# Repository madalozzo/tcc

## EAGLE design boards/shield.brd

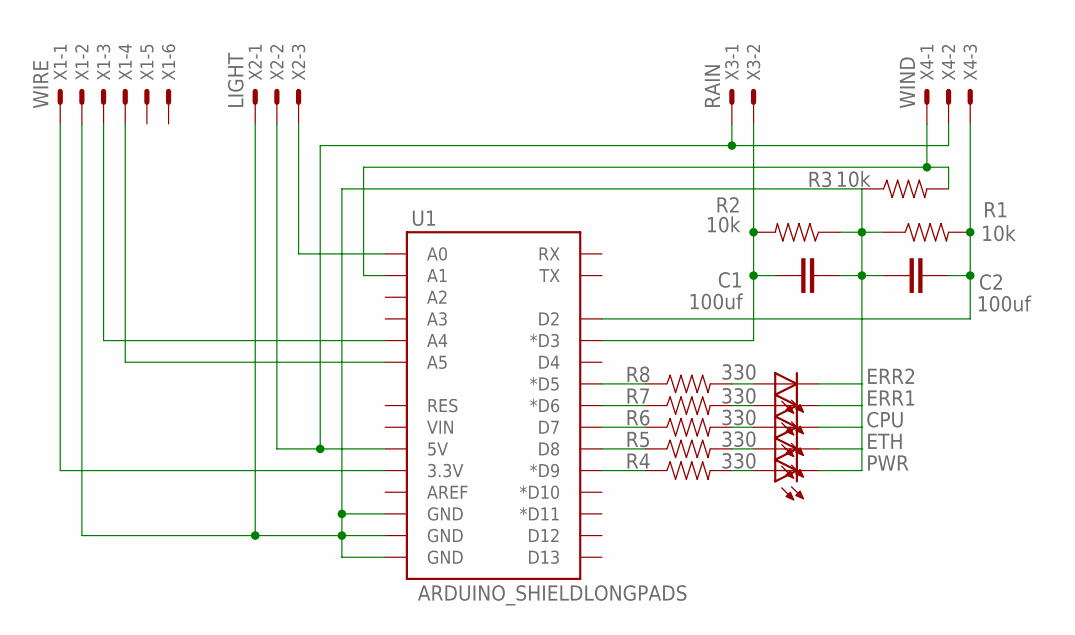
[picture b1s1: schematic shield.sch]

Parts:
C1, C2: 100uf; CAP-PTH-SMALL-KIT
CPU: LED3MM
ERR1, ERR2: LED3MM
ETH: LED3MM
PWR: LED3MM
R1, R2, R3: 10k; AXIAL-0.3-KIT
R4, R5, R6, R7, R8: 330; AXIAL-0.3-KIT
U1: ARDUINO_SHIELDLONGPADS; DUEMILANOVE_SHIELD_LONGPADS
X1: WIRE; 22-23-2061
X2: LIGHT; 22-23-2031
X3: RAIN; 22-23-2021
X4: WIND; 22-23-2031

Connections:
GND: C1.2, C2.1, CPU.K (C), ERR1.K (C), ERR2.K (C), ETH.K (C), PWR.K (C), R1.P$1 (1), R2.P$1 (1), R3.P$1 (1), U1.GND@0 (GND), U1.GND@1 (GND), U1.GND@2 (GND), X1.2, X2.1
INT0: C2.2, R1.P$2 (2), U1.D2, X4.3
INT1: C1.1, R2.P$2 (2), U1.D3 (*D3), X3.2
unnamed: U1.3.3V, X1.1
unnamed: R8.P$1 (1), U1.D5 (*D5)
unnamed: U1.5V, X2.2, X3.1, X4.2
unnamed: U1.A0, X2.3
unnamed: R3.P$2 (2), U1.A1, X4.1
unnamed: R7.P$1 (1), U1.D6 (*D6)
unnamed: R6.P$1 (1), U1.D7
unnamed: ERR2.A, R8.P$2 (2)
unnamed: R5.P$1 (1), U1.D8
unnamed: ERR1.A, R7.P$2 (2)
unnamed: CPU.A, R6.P$2 (2)
unnamed: ETH.A, R5.P$2 (2)
unnamed: PWR.A, R4.P$2 (2)
unnamed: R4.P$1 (1), U1.D9 (*D9)
SCL: U1.A5, X1.4
SDA: U1.A4, X1.3

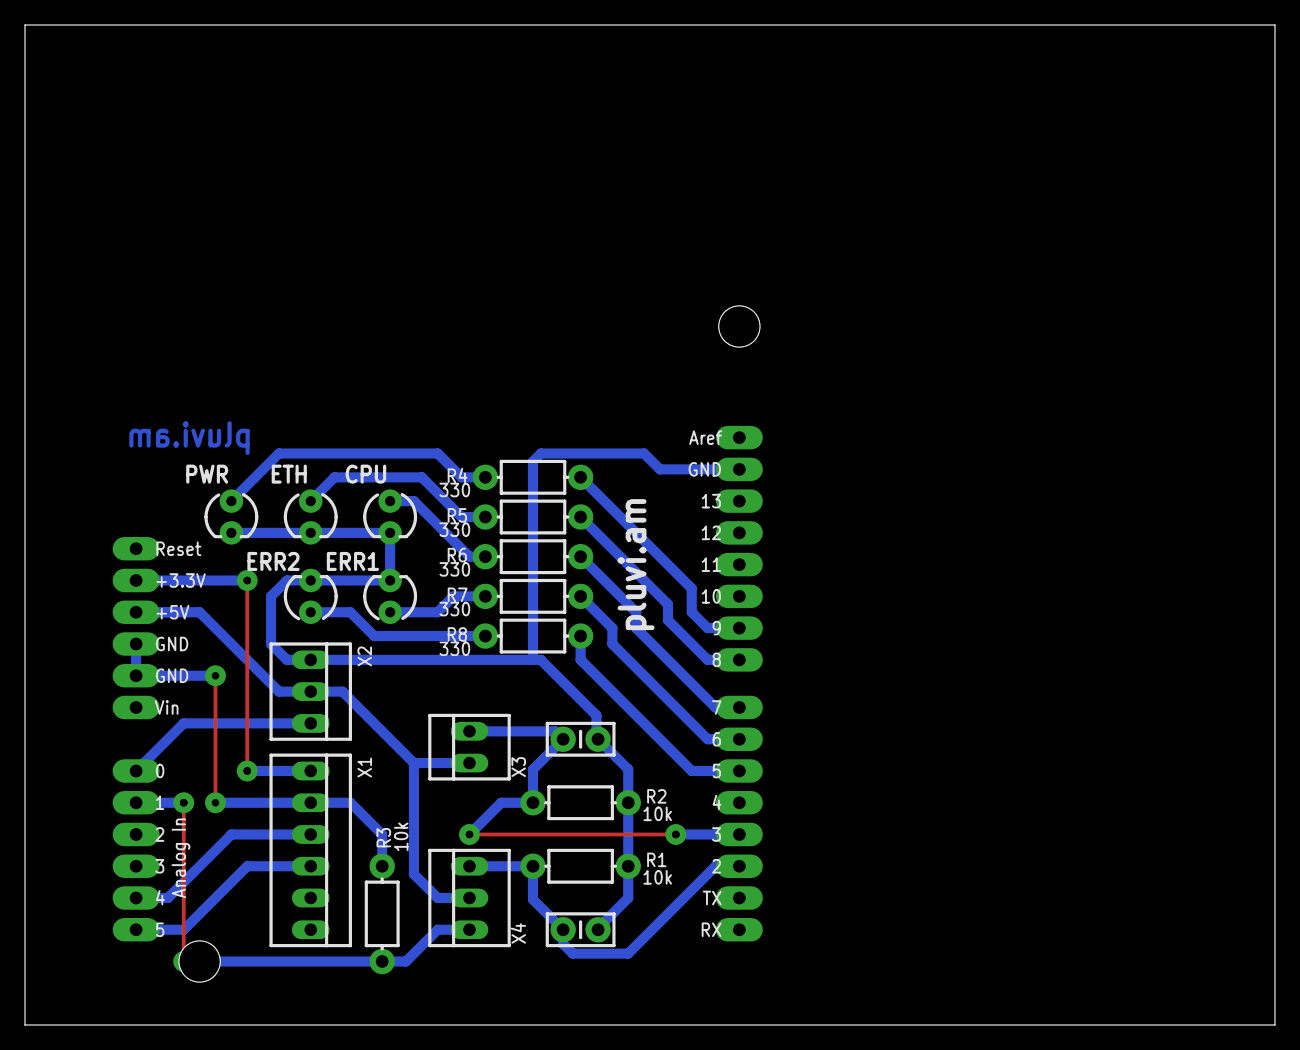
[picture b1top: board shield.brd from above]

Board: 2 copper layers, 100.0 x 80.0 mm, 20 parts (0 on the bottom side), 19 nets.

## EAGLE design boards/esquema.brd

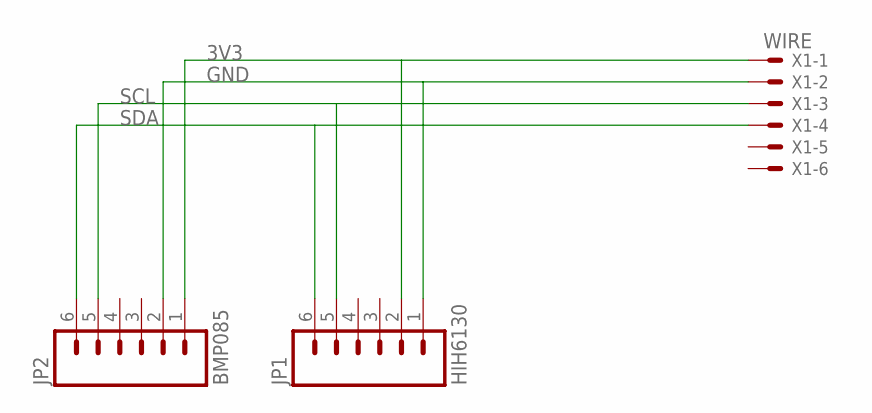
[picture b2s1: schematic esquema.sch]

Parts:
JP1: HIH6130; 1X06
JP2: BMP085; 1X06
X1: WIRE; 22-23-2061

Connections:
3V3: JP1.2, JP2.1, X1.1
GND: JP1.1, JP2.2, X1.2
SCL: JP1.5, JP2.5, X1.3
SDA: JP1.6, JP2.6, X1.4

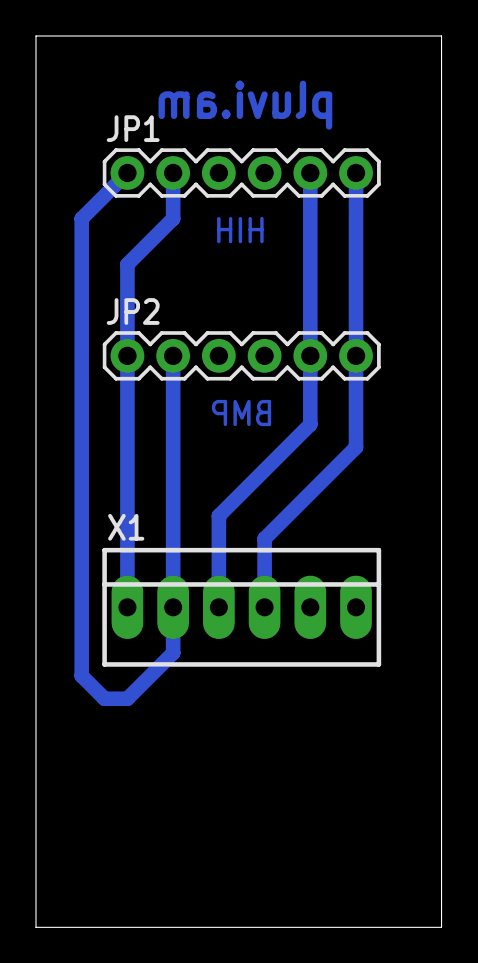
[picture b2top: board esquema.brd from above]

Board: 2 copper layers, 22.5 x 49.5 mm, 3 parts (0 on the bottom side), 4 nets.
